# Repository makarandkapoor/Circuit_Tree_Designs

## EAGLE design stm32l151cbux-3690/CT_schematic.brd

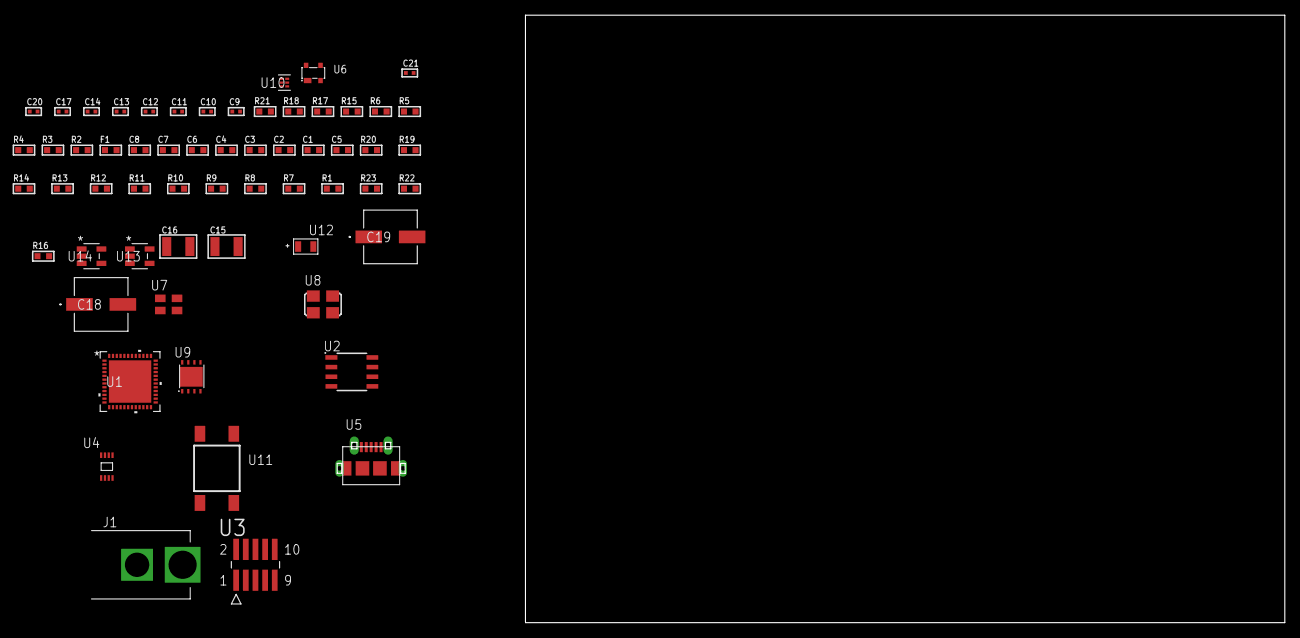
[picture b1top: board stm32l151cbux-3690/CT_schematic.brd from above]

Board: 2 copper layers, 124.8 x 80.0 mm, 60 parts (0 on the bottom side), 35 nets, no tracks yet.

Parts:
C1, C2, C3, C4, C6: 1e-07; C0603
C5: 4.7e-06; C0603
C7: 1e-08; C0603
C8: 1e-06; C0603
C9, C11, C12, C13, C14, C20, C21: 1e-08; C0402
C10, C17: 1e-07; C0402
C15, C16: 1e-05; C1210
C18, C19: 0.0001; EXV-9H
F1: 240.0; L0603
J1: PJ-037B; PJ-037B_PACKAGE
R1, R7, R8, R9, R10, R11, R12, R13, R14, R19, R20: 10000.0; R0603
R2, R18: 1000.0; R0603
R3: 1600.5; R0603
R4: 4700.0; R0603
R5, R6: 2200.0; R0603
R15: 5.0; R0603
R16: 100000.0; R0603
R17: 2231.0; R0603
R21: 9100.0; R0603
R22: 680000.0; R0603
R23: 120000.0; R0603
U1: STM32L151CBU6; UFQFPN48
U2: AT25512N-SH-T; SOIC-8
U3: FTSH-105-01-L-DV-K; SAMTEC_FTSH-105-01-L-DV-K
U4: 24AA08T-I/MNY; TDFN-8/6MM
U5: 47590-0001; MICRO_USB_AB
U6: prtr5v0u2ax; SOT143B
U7: ASEK-32.768KHz-ECST; ASEK
U8: ASFL1-25MHZ-NCS; ASFL1
U9: LP3878SDX-ADJ/NOPB; WSON-8
U10: TPS3895ADRYR; SON-6
U11: 4-1437565-2; SW_4-1437565-2
U12: Q65110A2395; LGM67K-G1J2-24-Z
U13, U14: nc7sz125m5x; NC7SZ125M5X

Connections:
CLK_U1_3: U1.3, U7.3
CLK_U1_5: U1.5, U8.3
GND: C1.2, C2.2, C3.2, C4.2, C5.2, C6.2, C7.2, C8.2, C9.2, C10.2, C11.2, C12.2, C13.2, C14.2, C15.2, C16.2, C17.2, C18.2, C19.2, C20.2, C21.2, J1.2, R2.2, R7.2, R14.2, R15.2, R18.2, R21.2, R23.2, U1.8, U1.23, U1.35, U1.47, U1.49, U2.4, U3.3, U3.5, U4.4, U5.5, U5.6, U5.7, U5.8, U5.9, U6.1, U7.2, U8.2, U9.3, U9.PAD, U10.2, U12.C, U13.2, U13.3, U14.1, U14.3
NET_U1_1: C6.1, U1.1
NET_U1_7: R4.1, U1.7, U14.4
NET_U1_9: C7.1, C8.1, F1.1, U1.9
NET_U1_42: R5.1, U1.42, U4.6
NET_U1_43: R6.1, U1.43, U4.5
NET_U1_44: R7.1, U1.44
NET_U1_45: R3.1, U1.45, U12.A
NET_U1_46: R1.1, U1.46, U11.3, U11.4
NET_U2_3: R8.1, U2.3
NET_U2_7: R10.1, U2.7
NET_U3_9: R15.1, U3.9
NET_U6_4: U5.1, U6.4
NET_U9_1: C14.1, U9.1
NET_U9_6: R17.2, R18.1, U9.6
NET_U9_8: R16.1, U9.8
NET_U10_1: R20.1, R21.1, U10.1
NET_U10_3: R22.2, R23.1, U10.3
NET_U10_4: R19.1, U10.4, U13.4, U14.2
NET_U11_1: R2.1, U11.1, U11.2
PROC_SPI1_MISO: U1.16, U2.2
PROC_SPI1_MOSI: U1.17, U2.5
PROC_SPI1_NSS: R9.1, U1.14, U2.1
PROC_SPI1_SCK: U1.15, U2.6
PROC_SYS_JTCK_SWCLK: R14.1, U1.37, U3.4
PROC_SYS_JTDI: R12.1, U1.38, U3.8
PROC_SYS_JTDO_TRACESWO: U1.39, U3.6
PROC_SYS_JTMS_SWDIO: R13.1, U1.34, U3.2
PROC_USB_DM: U1.32, U5.2, U6.3
PROC_USB_DP: U1.33, U5.3, U6.2
RST_OUT_U3_JTAG_RST_B: R11.1, U3.10, U13.1
VCC_S1_14V2: C15.1, C18.1, C19.1, J1.1, R16.2, U9.4
VCC_TIER1_3V3: C1.1, C2.1, C3.1, C4.1, C5.1, C9.1, C10.1, C11.1, C12.1, C13.1, C16.1, C17.1, C20.1, C21.1, F1.2, R1.2, R3.2, R4.2, R5.2, R6.2, R8.2, R9.2, R10.2, R11.2, R12.2, R13.2, R17.1, R19.2, R20.2, R22.1, U1.24, U1.36, U1.48, U2.8, U3.1, U4.7, U4.8, U7.4, U8.4, U9.5, U10.6, U13.5, U14.5

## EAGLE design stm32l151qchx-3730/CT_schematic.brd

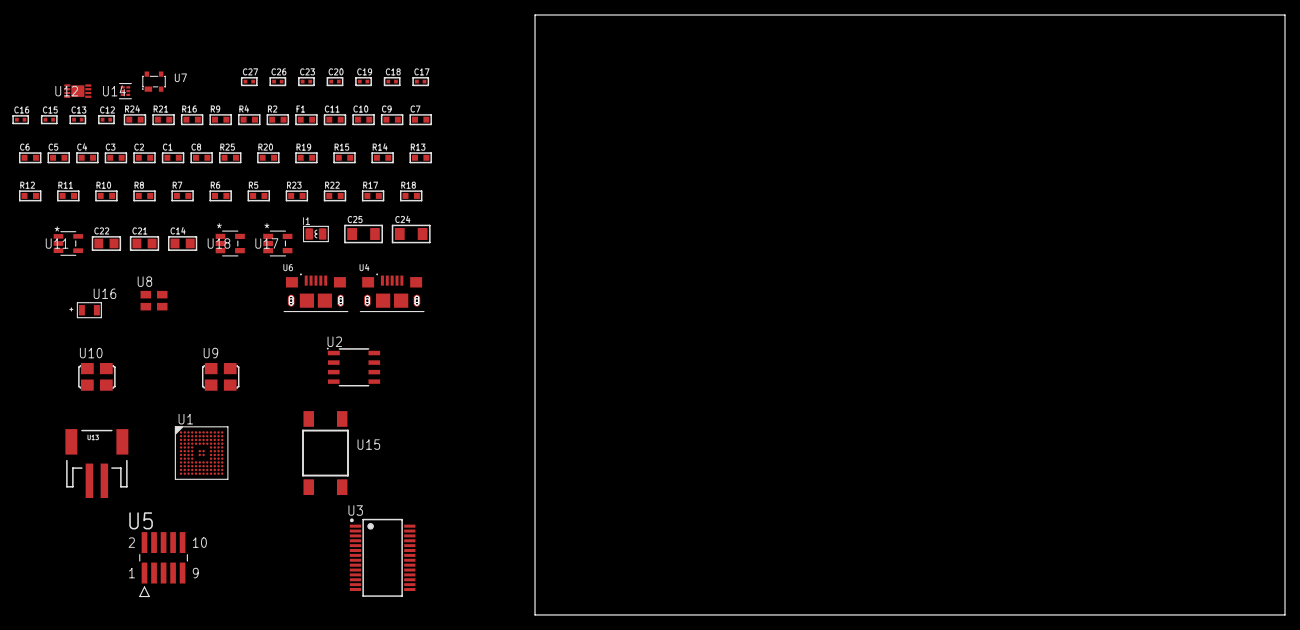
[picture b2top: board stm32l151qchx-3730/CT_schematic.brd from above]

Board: 2 copper layers, 70 parts (0 on the bottom side), 45 nets, no tracks yet.

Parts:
C1, C2, C3, C4, C5, C6, C7, C9: 1e-07; C0603
C8: 4.7e-06; C0603
C10: 1e-08; C0603
C11: 1e-06; C0603
C12, C18, C19, C20, C26, C27: 1e-08; C0402
C13, C15, C16, C17, C23: 1e-07; C0402
C14: 4.7e-06; C0805
C21, C22: 1e-05; C0805
C24, C25: 1e-05; C1206
F1: 240.0; L0603
I1: 1.5e-06; L0806
R2: 1000.0; R0603
R4, R9: 4700.0; R0603
R5, R6, R7, R8, R10, R11, R12, R13, R14, R15, R19, R20, R25: 10000.0; R0603
R16: 5.0; R0603
R17: 220000.0; R0603
R18: 1000000.0; R0603
R21: 9100.0; R0603
R22: 680000.0; R0603
R23: 120000.0; R0603
R24: 2000.0; R0603
U1: STM32L151QCH6; UFBGA132
U2: AT25M02-SSHD-T; SOIC-8
U3: FT232RL-REEL; SSOP-28
U4, U6: 10118193-0001LF; FCI_10118193-0001LF
U5: FTSH-105-01-L-DV-K; SAMTEC_FTSH-105-01-L-DV-K
U7: prtr5v0u2ax; SOT143B
U8: ASEK-32.768KHz-ECST; ASEK
U9: ASFL1-12MHZ-NCS; ASFL1
U10: ASFL1-25MHZ-NCS; ASFL1
U11: ltc3406es5; TSOT-23-5
U12: MCP73831T-2ACI/MC; DFN8_2X3MC
U13: S2B-PH-SM4-TB(LF)(SN); JST-2-SMD
U14: TPS3895ADRYR; SON-6
U15: 4-1437565-2; SW_4-1437565-2
U16: Q65110A2395; LGM67K-G1J2-24-Z
U17, U18: nc7sz125m5x; NC7SZ125M5X

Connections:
CLK_U1_D1: U1.D1, U8.3
CLK_U1_F1: U1.F1, U10.3
CLK_U3_27: U3.27, U9.3
GND: C1.2, C2.2, C3.2, C4.2, C5.2, C6.2, C7.2, C8.2, C9.2, C10.2, C11.2, C12.2, C13.2, C14.2, C15.2, C16.2, C17.2, C18.2, C19.2, C20.2, C21.2, C22.1, C22.2, C23.2, C24.2, C25.2, C26.2, C27.2, R2.2, R5.2, R11.2, R15.2, R16.2, R17.2, R21.2, R23.2, R24.2, U1.D3, U1.E3, U1.F2, U1.F6, U1.F7, U1.F11, U1.F12, U1.J1, U2.4, U3.7, U3.18, U3.21, U3.25, U3.26, U4.5, U4.6, U4.7, U4.8, U4.9, U5.3, U5.5, U6.5, U6.6, U6.7, U6.8, U6.9, U7.1, U8.2, U9.2, U10.2, U11.2, U12.6, U12.9, U13.2, U14.2, U16.C, U17.2, U17.3, U18.1, U18.3
INPUT_USBPOWER_5V: C24.1, R9.1, R25.2, U4.1, U12.1, U12.2
NET_U1_A4: R5.1, U1.A4
NET_U1_E2: C9.1, U1.E2
NET_U1_H2: R4.1, U1.H2, U18.4
NET_U1_M1: C10.1, C11.1, F1.1, U1.L1, U1.M1
NET_U1_M12: U15.3, U15.4
NET_U2_3: R6.1, U2.3
NET_U2_7: R8.1, U2.7
NET_U3_14: R10.1, U3.14
NET_U3_17: C15.1, U3.17
NET_U3_19: R11.1, U3.19
NET_U4_2: U3.16, U4.2
NET_U4_3: U3.15, U4.3
NET_U5_9: R16.1, U5.9
NET_U7_4: U6.1, U7.4
NET_U11_3: I1.1, U11.3
NET_U11_5: R17.1, R18.1, U11.5
NET_U11_ATNET_3: I1.2, R18.2
NET_U12_5: R25.1, U12.5
NET_U12_8: R24.1, U12.8
NET_U14_1: R20.1, R21.1, U14.1
NET_U14_3: R22.2, R23.1, U14.3
NET_U14_4: R19.1, U14.4, U17.4, U18.2
NET_U15_1: R2.1, U15.1, U15.2
PROC_SPI1_MISO: U1.A7, U2.2
PROC_SPI1_MOSI: U1.C5, U2.5
PROC_SPI1_NSS: R7.1, U1.J4, U2.1
PROC_SPI1_SCK: U1.K4, U2.6
PROC_SYS_JTCK_SWCLK: R15.1, U1.A10, U5.4
PROC_SYS_JTDI: R13.1, U1.A9, U5.8
PROC_SYS_JTDO_TRACESWO: U1.A8, U5.6
PROC_SYS_JTMS_SWDIO: R14.1, U1.A11, U5.2
PROC_USART2_CTS: U1.B8, U3.3
PROC_USART2_RTS: U1.B7, U3.11
PROC_USART2_RX: U1.B6, U3.1
PROC_USART2_TX: U1.A6, U3.5
PROC_USB_DM: U1.B12, U6.2, U7.3
PROC_USB_DP: U1.A12, U6.3, U7.2
RST_OUT_U5_JTAG_RST_B: R12.1, U5.10, U17.1
VCC_S1_3V7: C21.1, C25.1, U11.4, U12.3, U12.4, U13.1
VCC_TIER1_3V3: C1.1, C2.1, C3.1, C4.1, C5.1, C6.1, C7.1, C8.1, C12.1, C13.1, C14.1, C16.1, C17.1, C18.1, C19.1, C20.1, C22.2, C23.1, C26.1, C27.1, F1.2, I1.2, R4.2, R6.2, R7.2, R8.2, R10.2, R12.2, R13.2, R14.2, R18.2, R19.2, R20.2, R22.1, U1.C4, U1.G2, U1.G6, U1.G7, U1.G11, U1.G12, U1.H3, U2.8, U3.4, U3.20, U5.1, U8.4, U9.4, U10.4, U14.6, U17.5, U18.5

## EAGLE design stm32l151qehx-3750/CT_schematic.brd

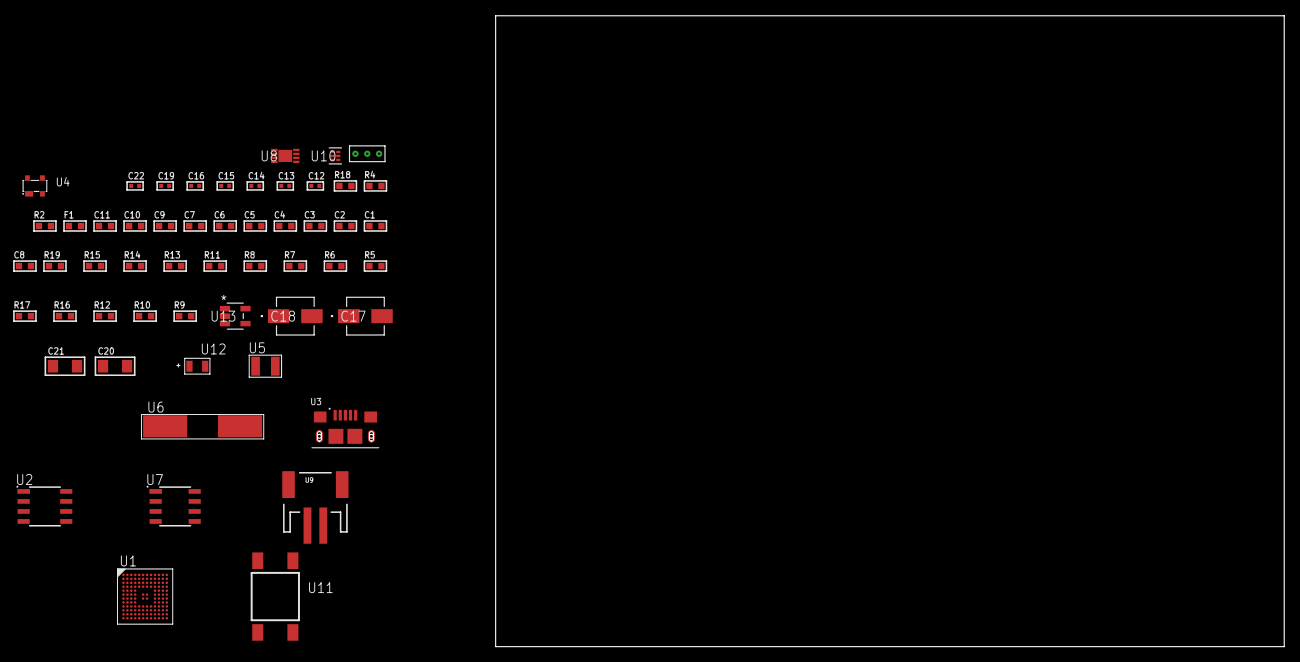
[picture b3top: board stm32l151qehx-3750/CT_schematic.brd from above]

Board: 2 copper layers, 122.6 x 80.0 mm, 54 parts (0 on the bottom side), 32 nets, no tracks yet.

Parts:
C1, C2, C3, C4, C5, C6, C7, C9: 1e-07; C0603
C8: 4.7e-06; C0603
C10: 1e-08; C0603
C11: 1e-06; C0603
C12, C13, C14, C15: 1e-11; C0402
C16, C22: 1e-08; C0402
C17: 1e-06; EXV-9B
C18: 2.2e-06; EXV-9B
C19: 1e-07; C0402
C20, C21: 1e-05; C1206
F1: 240.0; L0603
R2: 1000.0; R0603
R4: 4700.0; R0603
R5, R6, R7, R8, R13, R14, R19: 10000.0; R0603
R9, R10, R12: 100000.0; R0603
R11: 47000.0; R0603
R15: 82000.0; R0603
R16: 300000.0; R0603
R17: 120000.0; R0603
R18: 2000.0; R0603
U1: STM32L151QEH6; UFBGA132
U2: AT25160B-SSHL-T; SOIC-8
U3: 10118193-0001LF; FCI_10118193-0001LF
U4: prtr5v0u2ax; SOT143B
U5: ABS07-32.768KHZ-7-T
U6: ABLS-25.000MHZ-B2F-T
U7: LP2954AIMX/NOPB; LP2954
U8: MCP73831T-2ACI/MC; DFN8_2X3MC
U9: S2B-PH-SM4-TB(LF)(SN); JST-2-SMD
U10: TPS3895ADRYR; SON-6
U11: 4-1437565-2; SW_4-1437565-2
U12: Q65110A2395; LGM67K-G1J2-24-Z
U13: nc7sz125m5x; NC7SZ125M5X
U14: Dummy; DUMMY_PACKAGE_117

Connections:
CLK_CRYSTAL_U1_D1: C12.1, U1.D1, U5.1
CLK_CRYSTAL_U1_E1: C13.1, U1.E1, U5.2
CLK_CRYSTAL_U1_F1: C14.1, U1.F1, U6.1
CLK_CRYSTAL_U1_G1: C15.1, U1.G1, U6.2
GND: C1.2, C2.2, C3.2, C4.2, C5.2, C6.2, C7.2, C8.2, C9.2, C10.2, C11.2, C12.2, C13.2, C14.2, C15.2, C16.2, C17.2, C18.2, C19.2, C20.2, C21.2, C22.2, R2.2, R5.2, R12.2, R15.2, R17.2, R18.2, U1.D3, U1.E3, U1.F2, U1.F6, U1.F7, U1.F11, U1.F12, U1.J1, U2.4, U3.5, U3.6, U3.7, U3.8, U3.9, U4.1, U7.4, U8.6, U8.9, U9.2, U10.2, U12.C, U13.1, U13.3, U14.1
INPUT_USBPOWER_5V: C20.1, R19.2, U3.1, U4.4, U8.1, U8.2
NET_U1_A4: R5.1, U1.A4
NET_U1_E2: C9.1, U1.E2
NET_U1_H2: R4.1, U1.H2, U13.4
NET_U1_M1: C10.1, C11.1, F1.1, U1.L1, U1.M1
NET_U1_M12: U11.3, U11.4
NET_U2_3: R6.1, U2.3
NET_U2_7: R8.1, U2.7
NET_U7_3: R10.1, U7.3
NET_U7_5: R9.1, U7.5
NET_U7_7: R11.2, R12.1, U7.7
NET_U8_5: R19.1, U8.5
NET_U8_8: R18.1, U8.8
NET_U10_1: R14.1, R15.1, U10.1
NET_U10_3: R16.2, R17.1, U10.3
NET_U10_4: R13.1, U10.4, U13.2
NET_U11_1: R2.1, U11.1, U11.2
PROC_PE1: U1.A2, U14.3
PROC_PE3: U1.A1, U14.2
PROC_SPI1_MISO: U1.A7, U2.2
PROC_SPI1_MOSI: U1.C5, U2.5
PROC_SPI1_NSS: R7.1, U1.A9, U2.1
PROC_SPI1_SCK: U1.A8, U2.6
PROC_USB_DM: U1.B12, U3.2, U4.3
PROC_USB_DP: U1.A12, U3.3, U4.2
VCC_S1_3V7: C17.1, C21.1, R10.2, U7.8, U8.3, U8.4, U9.1
VCC_TIER1_1V8: C1.1, C2.1, C3.1, C4.1, C5.1, C6.1, C7.1, C8.1, C16.1, C18.1, C19.1, C22.1, F1.2, R4.2, R6.2, R7.2, R8.2, R9.2, R11.1, R13.2, R14.2, R16.1, U1.C4, U1.G2, U1.G6, U1.G7, U1.G11, U1.G12, U1.H3, U2.8, U7.1, U10.6, U13.5

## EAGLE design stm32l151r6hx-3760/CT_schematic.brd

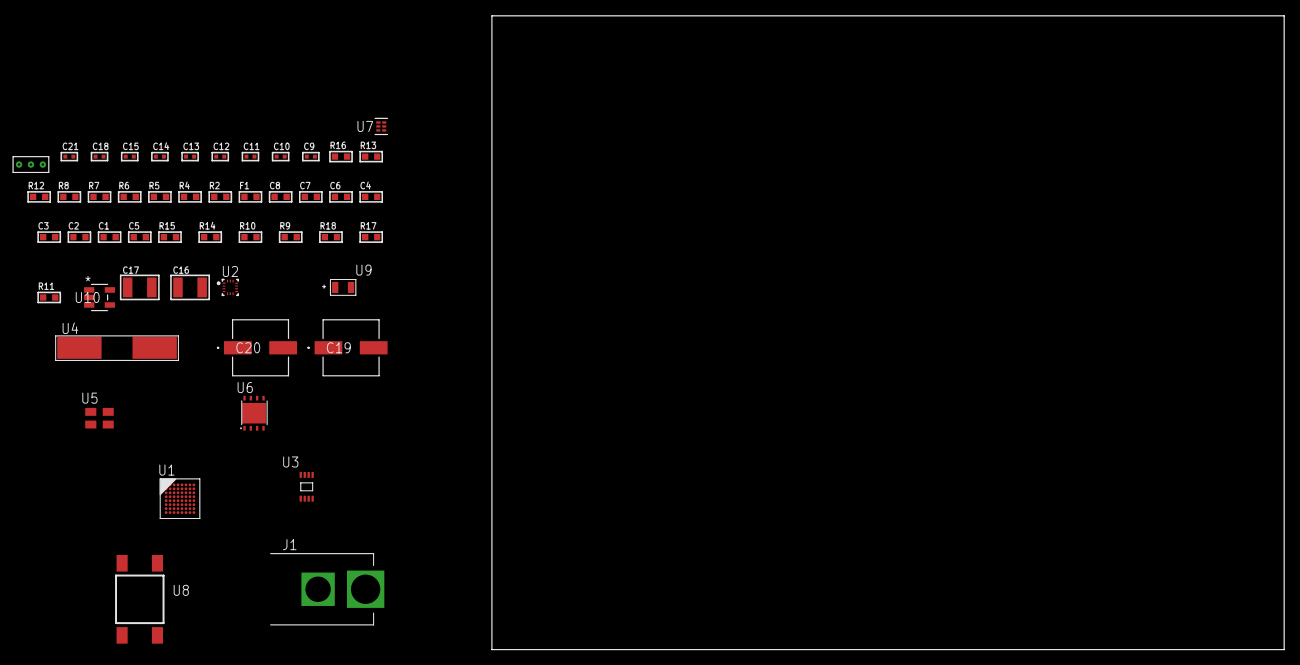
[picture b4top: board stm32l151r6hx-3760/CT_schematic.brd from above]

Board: 2 copper layers, 100.0 x 80.0 mm, 50 parts (0 on the bottom side), 24 nets, no tracks yet.

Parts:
C1, C2, C3, C4, C6: 1e-07; C0603
C5: 4.7e-06; C0603
C7: 1e-08; C0603
C8: 1e-06; C0603
C9, C10: 1e-11; C0402
C11, C12, C18: 1e-07; C0402
C13, C14, C15, C21: 1e-08; C0402
C16, C17: 1e-05; C1210
C19, C20: 0.0001; EXV-9H
F1: 240.0; L0603
J1: PJ-037B; PJ-037B_PACKAGE
R2, R13: 1000.0; R0603
R4: 4700.0; R0603
R5, R6, R7, R8: 2200.0; R0603
R9, R10, R14, R15: 10000.0; R0603
R11: 100000.0; R0603
R12: 2231.0; R0603
R16: 9100.0; R0603
R17: 680000.0; R0603
R18: 120000.0; R0603
U1: STM32L151R6H6; TFBGA64
U2: BMC150; LGA14R35P5X6_200X200X100
U3: 24AA02T-I/MNY; TDFN-8/6MM
U4: ABLS-25.000MHZ-B2F-T
U5: ASEK-32.768KHz-ECST; ASEK
U6: LP3878SDX-ADJ/NOPB; WSON-8
U7: TPS3895ADRYR; SON-6
U8: 4-1437565-2; SW_4-1437565-2
U9: Q65110A2395; LGM67K-G1J2-24-Z
U10: nc7sz125m5x; NC7SZ125M5X
U11: Dummy; DUMMY_PACKAGE_110

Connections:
CLK_CRYSTAL_U1_C1: C9.1, U1.C1, U4.1
CLK_CRYSTAL_U1_D1: C10.1, U1.D1, U4.2
CLK_U1_A1: U1.A1, U5.3
GND: C1.2, C2.2, C3.2, C4.2, C5.2, C6.2, C7.2, C8.2, C9.2, C10.2, C11.2, C12.2, C13.2, C14.2, C15.2, C16.2, C17.2, C18.2, C19.2, C20.2, C21.2, J1.2, R2.2, R9.2, R13.2, R16.2, R18.2, U1.C2, U1.D4, U1.D5, U1.D6, U1.F1, U2.1, U2.6, U2.7, U2.9, U3.4, U3.7, U5.2, U6.3, U6.PAD, U7.2, U9.C, U10.1, U10.3, U11.1
NET_U1_A3: R6.1, U1.A3, U2.14
NET_U1_B2: C6.1, U1.B2
NET_U1_B3: R5.1, U1.B3, U2.11
NET_U1_B4: R9.1, U1.B4
NET_U1_E1: R4.1, U1.E1, U10.4
NET_U1_G7: R7.1, U1.G7, U3.6
NET_U1_H1: C7.1, C8.1, F1.1, U1.G1, U1.H1
NET_U1_H7: R8.1, U1.H7, U3.5
NET_U1_H8: U8.3, U8.4
NET_U6_1: C15.1, U6.1
NET_U6_6: R12.2, R13.1, U6.6
NET_U6_8: R11.1, U6.8
NET_U7_1: R15.1, R16.1, U7.1
NET_U7_3: R17.2, R18.1, U7.3
NET_U7_4: R14.1, U7.4, U10.2
NET_U8_1: R2.1, U8.1, U8.2
PROC_PB4: U1.A4, U11.3
PROC_PC13_WKUP2: U1.A2, U11.2
VCC_S1_13V5: C16.1, C19.1, C20.1, J1.1, R11.2, U6.4
VCC_TIER1_3V3: C1.1, C2.1, C3.1, C4.1, C5.1, C11.1, C12.1, C13.1, C14.1, C17.1, C18.1, C21.1, F1.2, R4.2, R5.2, R6.2, R7.2, R8.2, R10.1, R10.2, R12.1, R14.2, R15.2, R17.1, U1.D2, U1.E4, U1.E5, U1.E6, U2.8, U2.10, U2.12, U2.13, U3.8, U5.4, U6.5, U7.6, U10.5

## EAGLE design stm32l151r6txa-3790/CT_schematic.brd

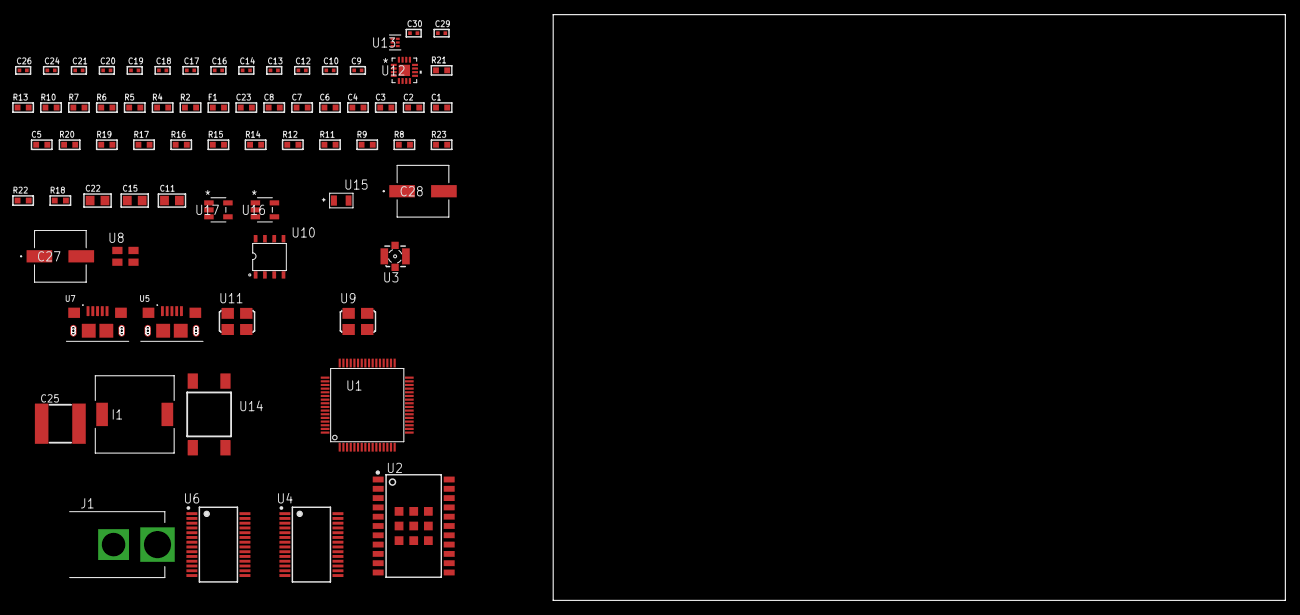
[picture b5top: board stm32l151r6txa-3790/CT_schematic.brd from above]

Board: 2 copper layers, 165.8 x 80.0 mm, 71 parts (0 on the bottom side), 50 nets, no tracks yet.

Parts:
C1, C2, C3, C4, C6: 1e-07; C0603
C5: 4.7e-06; C0603
C7: 1e-08; C0603
C8, C23: 1e-06; C0603
C9, C10, C12, C13, C14, C16, C17, C24, C26: 1e-07; C0402
C11, C15: 4.7e-06; C0805
C18, C19, C20, C21, C29, C30: 1e-08; C0402
C22: 1e-05; C0805
C25: 6.8e-05; 2220
C27, C28: 0.0001; EXV-9H
F1: 240.0; L0603
I1: 3.8e-06; DR1040
J1: PJ-037B; PJ-037B_PACKAGE
R2: 1000.0; R0603
R4, R5, R10, R13: 4700.0; R0603
R6, R7: 2200.0; R0603
R8, R9, R11, R12, R14, R15, R19, R20: 10000.0; R0603
R16: 20000.0; R0603
R17: 91000.0; R0603
R18: 300000.0; R0603
R21: 9100.0; R0603
R22: 680000.0; R0603
R23: 120000.0; R0603
U1: STM32L151R6T6A; LQFP64
U2: A2200-A
U3: 73412-0114; COAXIAL_C
U4, U6: FT232RL-REEL; SSOP-28
U5, U7: 10118193-0001LF; FCI_10118193-0001LF
U8: ASEK-32.768KHz-ECST; ASEK
U9: ASFL1-12MHZ-NCS; ASFL1
U10: idt74fct38072; IDT74FCT38072
U11: ASFL1-25MHZ-NCS; ASFL1
U12: LTC3601EUD#PBF; QFN-16_EP
U13: TPS3895ADRYR; SON-6
U14: 4-1437565-2; SW_4-1437565-2
U15: Q65110A2395; LGM67K-G1J2-24-Z
U16, U17: nc7sz125m5x; NC7SZ125M5X

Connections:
CLK_U1_3: U1.3, U8.3
CLK_U1_5: U1.5, U11.3
CLK_U4_27: U4.27, U10.7
CLK_U6_27: U6.27, U10.6
CLK_U10_3: U9.3, U10.3
GND: C1.2, C2.2, C3.2, C4.2, C5.2, C6.2, C7.2, C8.2, C9.2, C10.2, C11.2, C12.2, C13.2, C14.2, C15.2, C16.2, C17.2, C18.2, C19.2, C20.2, C21.2, C22.2, C23.2, C25.1, C25.2, C26.2, C27.2, C28.2, C29.2, C30.2, J1.2, R2.2, R8.2, R12.2, R15.2, R16.2, R18.2, R21.2, R23.2, U1.12, U1.18, U1.31, U1.47, U1.63, U2.7, U2.8, U2.23, U2.24, U2.25, U2.26, U2.27, U2.28, U2.29, U2.30, U2.31, U4.7, U4.18, U4.21, U4.25, U4.26, U5.5, U5.6, U5.7, U5.8, U5.9, U6.7, U6.18, U6.21, U6.25, U6.26, U7.5, U7.6, U7.7, U7.8, U7.9, U8.2, U9.2, U10.4, U10.5, U10.8, U11.2, U12.1, U12.9, U12.17, U13.2, U15.C, U16.1, U16.3, U17.1, U17.3
NET_U1_1: C6.1, U1.1
NET_U1_7: R5.1, U1.7, U17.4
NET_U1_13: C7.1, C8.1, F1.1, U1.13
NET_U1_58: R6.1, U1.58, U2.15
NET_U1_59: R7.1, U1.59, U2.16
NET_U1_60: R8.1, U1.60
NET_U1_62: U14.3, U14.4
NET_U2_2: R9.2, U2.2
NET_U2_17: R9.1, U2.17
NET_U2_22: R4.1, U2.22, U16.4
NET_U3_1: U2.11, U3.1
NET_U3_2: U2.10, U3.2, U3.3, U3.4
NET_U4_14: R11.1, U4.14
NET_U4_17: C12.1, U4.17
NET_U4_19: R12.1, U4.19
NET_U5_1: R10.1, U5.1
NET_U5_2: U4.16, U5.2
NET_U5_3: U4.15, U5.3
NET_U6_14: R14.1, U6.14
NET_U6_17: C16.1, U6.17
NET_U6_19: R15.1, U6.19
NET_U7_1: R13.1, U7.1
NET_U7_2: U6.16, U7.2
NET_U7_3: U6.15, U7.3
NET_U12_3: C24.2, I1.1, U12.3, U12.4
NET_U12_6: C24.1, U12.6
NET_U12_7: C23.1, U12.7, U12.12
NET_U12_10: R18.1, U12.10
NET_U12_11: R16.1, R17.1, U12.11
NET_U12_ATNET_3: I1.2, R17.2
NET_U13_1: R20.1, R21.1, U13.1
NET_U13_3: R22.2, R23.1, U13.3
NET_U13_4: R19.1, U13.4, U16.2, U17.2
NET_U14_1: R2.1, U14.1, U14.2
PROC_USART1_CTS: U1.44, U4.3
PROC_USART1_RTS: U1.45, U4.11
PROC_USART1_RX: U1.43, U4.1
PROC_USART1_TX: U1.42, U4.5
PROC_USART2_CTS: U1.14, U6.3
PROC_USART2_RTS: U1.15, U6.11
PROC_USART2_RX: U1.17, U6.1
PROC_USART2_TX: U1.16, U6.5
VCC_S1_7V0: C22.1, C27.1, C28.1, J1.1, U12.15, U12.16
VCC_TIER1_3V3: C1.1, C2.1, C3.1, C4.1, C5.1, C9.1, C10.1, C11.1, C13.1, C14.1, C15.1, C17.1, C18.1, C19.1, C20.1, C21.1, C25.2, C26.1, C29.1, C30.1, F1.2, I1.2, R4.2, R5.2, R6.2, R7.2, R11.2, R14.2, R17.2, R19.2, R20.2, R22.1, U1.19, U1.32, U1.48, U1.64, U2.20, U4.4, U4.20, U6.4, U6.20, U8.4, U9.4, U10.1, U10.2, U11.4, U12.8, U13.6, U16.5, U17.5

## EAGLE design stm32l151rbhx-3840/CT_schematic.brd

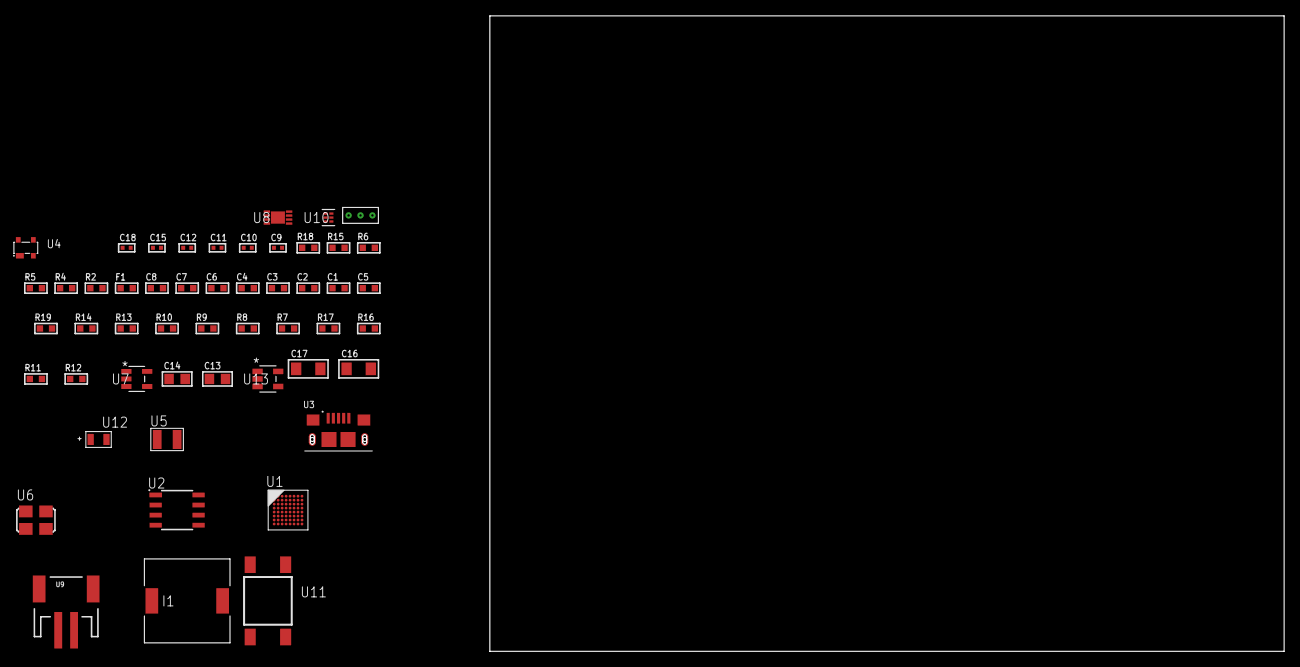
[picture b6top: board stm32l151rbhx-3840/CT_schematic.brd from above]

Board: 2 copper layers, 122.6 x 80.0 mm, 51 parts (0 on the bottom side), 30 nets, no tracks yet.

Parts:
C1, C2, C3, C4, C6: 1e-07; C0603
C5: 4.7e-06; C0603
C7: 1e-08; C0603
C8: 1e-06; C0603
C9, C10: 1e-11; C0402
C11, C12, C18: 1e-08; C0402
C13, C14: 1e-05; C0805
C15: 1e-07; C0402
C16, C17: 1e-05; C1206
F1: 240.0; L0603
I1: 3.8e-06; DR1040
R2: 1000.0; R0603
R4: 4700.0; R0603
R5, R6: 2200.0; R0603
R7, R8, R9, R10, R13, R14, R19: 10000.0; R0603
R11: 220000.0; R0603
R12: 1000000.0; R0603
R15: 9100.0; R0603
R16: 680000.0; R0603
R17: 120000.0; R0603
R18: 2000.0; R0603
U1: STM32L151RBH6; TFBGA64
U2: 24AA1025T-I/SN; SOIC-8
U3: 10118193-0001LF; FCI_10118193-0001LF
U4: prtr5v0u2ax; SOT143B
U5: ABS07-32.768KHZ-7-T
U6: ASFL1-25MHZ-NCS; ASFL1
U7: ltc3406es5; TSOT-23-5
U8: MCP73831T-2ACI/MC; DFN8_2X3MC
U9: S2B-PH-SM4-TB(LF)(SN); JST-2-SMD
U10: TPS3895ADRYR; SON-6
U11: 4-1437565-2; SW_4-1437565-2
U12: Q65110A2395; LGM67K-G1J2-24-Z
U13: nc7sz125m5x; NC7SZ125M5X
U14: Dummy; DUMMY_PACKAGE_110

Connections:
CLK_CRYSTAL_U1_A1: C9.1, U1.A1, U5.1
CLK_CRYSTAL_U1_B1: C10.1, U1.B1, U5.2
CLK_U1_C1: U1.C1, U6.3
GND: C1.2, C2.2, C3.2, C4.2, C5.2, C6.2, C7.2, C8.2, C9.2, C10.2, C11.2, C12.2, C13.2, C14.1, C14.2, C15.2, C16.2, C17.2, C18.2, R2.2, R7.2, R10.2, R11.2, R15.2, R17.2, R18.2, U1.C2, U1.D4, U1.D5, U1.D6, U1.F1, U2.4, U3.5, U3.6, U3.7, U3.8, U3.9, U4.1, U6.2, U7.2, U8.6, U8.9, U9.2, U10.2, U12.C, U13.1, U13.3, U14.1
INPUT_USBPOWER_5V: C16.1, R19.2, U3.1, U4.4, U8.1, U8.2
NET_U1_A3: R6.1, U1.A3, U2.5
NET_U1_B2: C6.1, U1.B2
NET_U1_B3: R5.1, U1.B3, U2.6
NET_U1_B4: R7.1, U1.B4
NET_U1_E1: R4.1, U1.E1, U13.4
NET_U1_H1: C7.1, C8.1, F1.1, U1.G1, U1.H1
NET_U1_H8: U11.3, U11.4
NET_U2_1: R9.1, U2.1
NET_U2_2: R10.1, U2.2
NET_U2_3: R8.1, U2.3
NET_U7_3: I1.1, U7.3
NET_U7_5: R11.1, R12.1, U7.5
NET_U7_ATNET_3: I1.2, R12.2
NET_U8_5: R19.1, U8.5
NET_U8_8: R18.1, U8.8
NET_U10_1: R14.1, R15.1, U10.1
NET_U10_3: R16.2, R17.1, U10.3
NET_U10_4: R13.1, U10.4, U13.2
NET_U11_1: R2.1, U11.1, U11.2
PROC_ADC_IN19: U1.G8, U14.3
PROC_ADC_IN20: U1.F8, U14.2
PROC_USB_DM: U1.C8, U3.2, U4.3
PROC_USB_DP: U1.B8, U3.3, U4.2
VCC_S1_3V7: C13.1, C17.1, U7.4, U8.3, U8.4, U9.1
VCC_TIER1_3V3: C1.1, C2.1, C3.1, C4.1, C5.1, C11.1, C12.1, C14.2, C15.1, C18.1, F1.2, I1.2, R4.2, R5.2, R6.2, R8.2, R9.2, R12.2, R13.2, R14.2, R16.1, U1.D2, U1.E4, U1.E5, U1.E6, U2.7, U2.8, U6.4, U10.6, U13.5

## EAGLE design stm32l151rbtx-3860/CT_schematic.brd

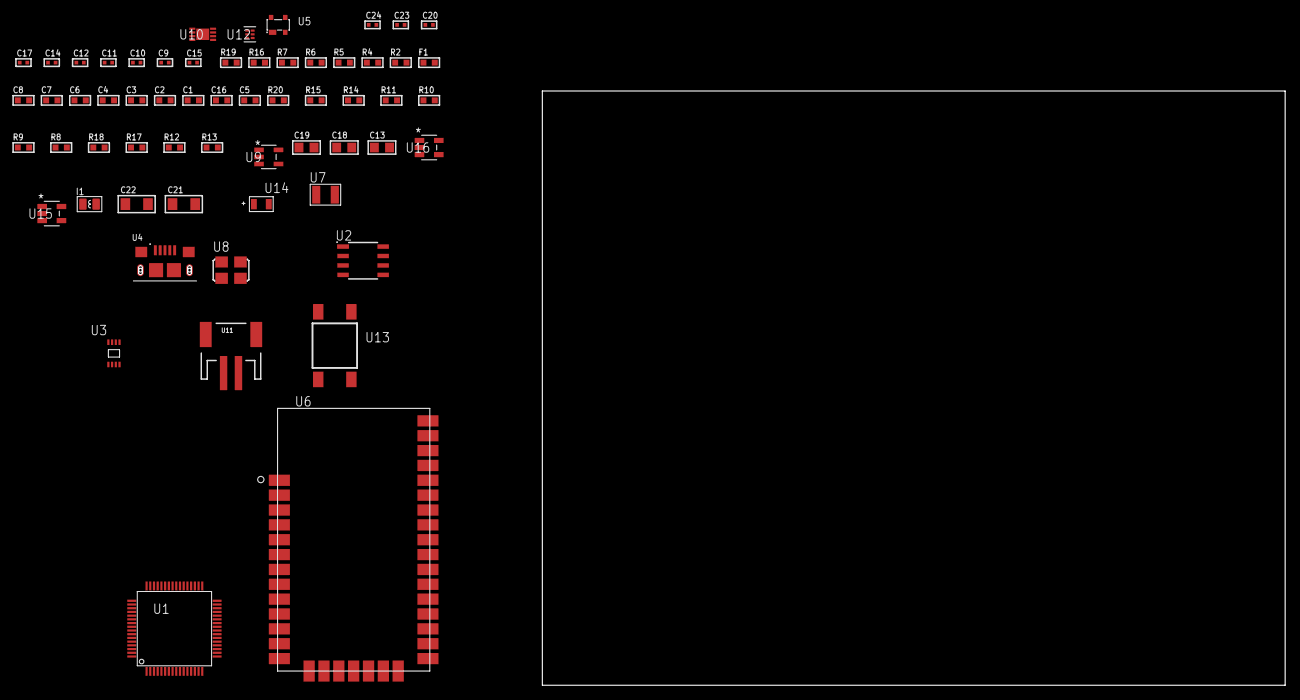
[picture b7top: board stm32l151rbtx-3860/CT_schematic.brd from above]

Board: 2 copper layers, 60 parts (0 on the bottom side), 36 nets, no tracks yet.

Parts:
C1, C2, C3, C4, C6: 1e-07; C0603
C5: 4.7e-06; C0603
C7: 1e-08; C0603
C8: 1e-06; C0603
C9, C10: 1e-11; C0402
C11, C12, C17, C23, C24: 1e-08; C0402
C13, C18, C19: 1e-05; C0805
C14, C20: 1e-07; C0402
C15: 4.7e-11; C0402
C16: 8.2e-12; C0603
C21, C22: 1e-05; C1206
F1: 240.0; L0603
I1: 3.3e-06; L0806
R2: 1000.0; R0603
R4, R5: 4700.0; R0603
R6, R7: 2200.0; R0603
R8, R9, R10, R11, R14, R15, R20: 10000.0; R0603
R12: 220000.0; R0603
R13: 1000000.0; R0603
R16: 9100.0; R0603
R17: 680000.0; R0603
R18: 120000.0; R0603
R19: 2000.0; R0603
U1: STM32L151RBT6; LQFP64
U2: AT25320B-SSHL-T; SOIC-8
U3: 24AA00T-I/MNY; TDFN-8/6MM
U4: 10118193-0001LF; FCI_10118193-0001LF
U5: prtr5v0u2ax; SOT143B
U6: XB24CZ7UIS-004
U7: ABS07-32.768KHZ-7-T
U8: ASFL1-25MHZ-NCS; ASFL1
U9: ltc3406es5; TSOT-23-5
U10: MCP73831T-2ACI/MC; DFN8_2X3MC
U11: S2B-PH-SM4-TB(LF)(SN); JST-2-SMD
U12: TPS3895ADRYR; SON-6
U13: 4-1437565-2; SW_4-1437565-2
U14: Q65110A2395; LGM67K-G1J2-24-Z
U15, U16: nc7sz125m5x; NC7SZ125M5X

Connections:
CLK_CRYSTAL_U1_3: C9.1, U1.3, U7.1
CLK_CRYSTAL_U1_4: C10.1, U1.4, U7.2
CLK_U1_5: U1.5, U8.3
GND: C1.2, C2.2, C3.2, C4.2, C5.2, C6.2, C7.2, C8.2, C9.2, C10.2, C11.2, C12.2, C13.2, C14.2, C15.2, C16.2, C17.2, C18.2, C19.1, C19.2, C20.2, C21.2, C22.2, C23.2, C24.2, R2.2, R8.2, R12.2, R16.2, R18.2, R19.2, U1.12, U1.18, U1.31, U1.47, U1.63, U2.4, U3.4, U4.5, U4.6, U4.7, U4.8, U4.9, U5.1, U6.1, U6.11, U6.13, U6.22, U6.35, U8.2, U9.2, U10.6, U10.9, U11.2, U12.2, U14.C, U15.1, U15.3, U16.1, U16.3
INPUT_USBPOWER_5V: C21.1, R20.2, U4.1, U5.4, U10.1, U10.2
NET_U1_1: C6.1, U1.1
NET_U1_7: R5.1, U1.7, U16.4
NET_U1_13: C7.1, C8.1, F1.1, U1.13
NET_U1_58: R6.1, U1.58, U3.6
NET_U1_59: R7.1, U1.59, U3.5
NET_U1_60: R8.1, U1.60
NET_U1_62: U13.3, U13.4
NET_U2_3: R9.1, U2.3
NET_U2_7: R11.1, U2.7
NET_U6_6: R4.1, U6.6, U15.4
NET_U9_3: I1.1, U9.3
NET_U9_5: R12.1, R13.1, U9.5
NET_U9_ATNET_3: I1.2, R13.2
NET_U10_5: R20.1, U10.5
NET_U10_8: R19.1, U10.8
NET_U12_1: R15.1, R16.1, U12.1
NET_U12_3: R17.2, R18.1, U12.3
NET_U12_4: R14.1, U12.4, U15.2, U16.2
NET_U13_1: R2.1, U13.1, U13.2
PROC_SPI1_MISO: U1.22, U6.17
PROC_SPI1_MOSI: U1.23, U6.16
PROC_SPI1_NSS: U1.20, U6.15
PROC_SPI1_SCK: U1.21, U6.14
PROC_SPI2_MISO: U1.35, U2.2
PROC_SPI2_MOSI: U1.36, U2.5
PROC_SPI2_NSS: R10.1, U1.33, U2.1
PROC_SPI2_SCK: U1.34, U2.6
PROC_USB_DM: U1.44, U4.2, U5.3
PROC_USB_DP: U1.45, U4.3, U5.2
VCC_S1_3V7: C18.1, C22.1, U9.4, U10.3, U10.4, U11.1
VCC_TIER1_3V3: C1.1, C2.1, C3.1, C4.1, C5.1, C11.1, C12.1, C13.1, C14.1, C15.1, C16.1, C17.1, C19.2, C20.1, C23.1, C24.1, F1.2, I1.2, R4.2, R5.2, R6.2, R7.2, R9.2, R10.2, R11.2, R13.2, R14.2, R15.2, R17.1, U1.19, U1.32, U1.48, U1.64, U2.8, U3.8, U6.2, U6.27, U8.4, U12.6, U15.5, U16.5

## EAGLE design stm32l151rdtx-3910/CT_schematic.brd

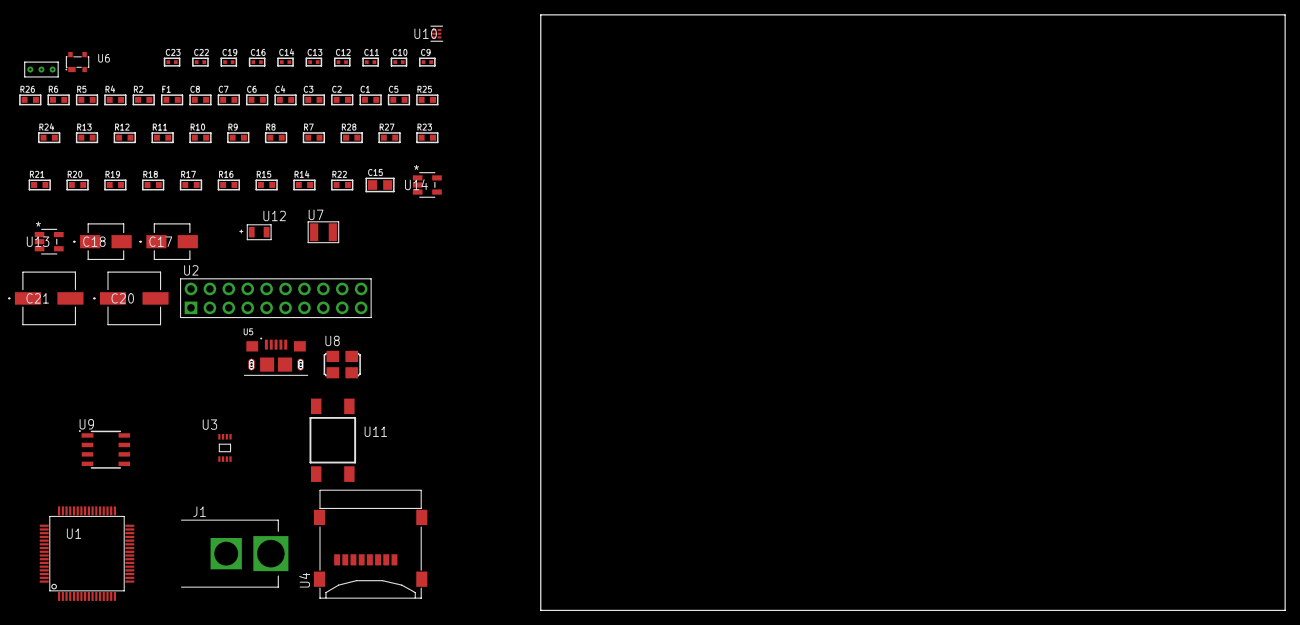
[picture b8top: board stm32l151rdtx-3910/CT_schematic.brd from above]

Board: 2 copper layers, 66 parts (0 on the bottom side), 38 nets, no tracks yet.

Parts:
C1, C2, C3, C4, C6: 1e-07; C0603
C5: 4.7e-06; C0603
C7: 1e-08; C0603
C8: 1e-06; C0603
C9, C10: 1e-11; C0402
C11, C12, C14, C19: 1e-07; C0402
C13, C16, C22, C23: 1e-08; C0402
C15: 1e-05; C0805
C17: 1e-06; EXV-9B
C18: 2.2e-06; EXV-9B
C20, C21: 0.0001; EXV-9H
F1: 240.0; L0603
J1: PJ-037B; PJ-037B_PACKAGE
R2: 1000.0; R0603
R4: 4700.0; R0603
R5, R6: 2200.0; R0603
R7, R8, R9, R10, R11, R12, R13, R24, R25: 10000.0; R0603
R14, R15, R16, R17, R18, R19, R20, R21, R23: 100000.0; R0603
R22: 164658.62; R0603
R26: 9100.0; R0603
R27: 680000.0; R0603
R28: 120000.0; R0603
U1: STM32L151RDT6; LQFP64
U2: TST-110-05-T-D-RA
U3: 24AA01T-I/MNY; TDFN-8/6MM
U4: 0472192001; MOLEX_47219-2001
U5: 10118193-0001LF; FCI_10118193-0001LF
U6: prtr5v0u2ax; SOT143B
U7: ABS07-32.768KHZ-7-T
U8: ASFL1-25MHZ-NCS; ASFL1
U9: LP2954AIMX/NOPB; LP2954
U10: TPS3895ADRYR; SON-6
U11: 4-1437565-2; SW_4-1437565-2
U12: Q65110A2395; LGM67K-G1J2-24-Z
U13, U14: nc7sz125m5x; NC7SZ125M5X
U15: Dummy; DUMMY_PACKAGE_144

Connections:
CLK_CRYSTAL_U1_3: C9.1, U1.3, U7.1
CLK_CRYSTAL_U1_4: C10.1, U1.4, U7.2
CLK_U1_5: U1.5, U8.3
GND: C1.2, C2.2, C3.2, C4.2, C5.2, C6.2, C7.2, C8.2, C9.2, C10.2, C11.2, C12.2, C13.2, C14.2, C15.2, C16.2, C17.2, C18.2, C19.2, C20.2, C21.2, C22.2, C23.2, J1.2, R2.2, R7.2, R13.2, R23.2, R26.2, R28.2, U1.12, U1.18, U1.31, U1.47, U1.63, U2.4, U2.6, U2.8, U2.10, U2.12, U2.14, U2.16, U2.18, U2.20, U3.4, U3.7, U4.6, U4.G1, U4.G2, U4.G3, U4.G4, U5.5, U5.6, U5.7, U5.8, U5.9, U6.1, U8.2, U9.4, U10.2, U12.C, U13.2, U13.3, U14.1, U14.3, U15.1
NET_U1_1: C6.1, U1.1
NET_U1_7: R4.1, U1.7, U14.4
NET_U1_13: C7.1, C8.1, F1.1, U1.13
NET_U1_58: R5.1, U1.58, U3.6
NET_U1_59: R6.1, U1.59, U3.5
NET_U1_60: R7.1, U1.60
NET_U1_62: U11.3, U11.4
NET_U2_19: R13.1, U2.19
NET_U6_4: U5.1, U6.4
NET_U9_3: R21.1, U9.3
NET_U9_5: R20.1, U9.5
NET_U9_7: R22.2, R23.1, U9.7
NET_U10_1: R25.1, R26.1, U10.1
NET_U10_3: R27.2, R28.1, U10.3
NET_U10_4: R24.1, U10.4, U13.4, U14.2
NET_U11_1: R2.1, U11.1, U11.2
PROC_PC13_WKUP2: U1.2, U15.2
PROC_PH1_OSC_OUT: U1.6, U15.3
PROC_SDIO_CK: R15.1, U1.53, U4.5
PROC_SDIO_CMD: R14.1, U1.54, U4.3
PROC_SDIO_D0: R16.1, U1.39, U4.7
PROC_SDIO_D1: R17.1, U1.40, U4.8
PROC_SDIO_D2: R18.1, U1.51, U4.1
PROC_SDIO_D3: R19.1, U1.52, U4.2
PROC_SYS_JTCK_SWCLK: R11.1, U1.49, U2.9
PROC_SYS_JTDI: R9.1, U1.50, U2.5
PROC_SYS_JTDO_TRACESWO: U1.55, U2.13
PROC_SYS_JTMS_SWDIO: R10.1, U1.46, U2.7
PROC_SYS_JTRST: R8.1, U1.56, U2.3
PROC_USB_DM: U1.44, U5.2, U6.3
PROC_USB_DP: U1.45, U5.3, U6.2
RST_OUT_U2_SRESET_B: R12.1, U2.15, U13.1
VCC_S1_11V8: C17.1, C20.1, C21.1, J1.1, R21.2, U9.8
VCC_TIER1_3V3: C1.1, C2.1, C3.1, C4.1, C5.1, C11.1, C12.1, C13.1, C14.1, C15.1, C16.1, C18.1, C19.1, C22.1, C23.1, F1.2, R4.2, R5.2, R6.2, R8.2, R9.2, R10.2, R11.2, R12.2, R14.2, R15.2, R16.2, R17.2, R18.2, R19.2, R20.2, R22.1, R24.2, R25.2, R27.1, U1.19, U1.32, U1.48, U1.64, U2.1, U2.2, U3.8, U4.4, U8.4, U9.1, U10.6, U13.5, U14.5
